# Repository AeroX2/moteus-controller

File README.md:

# moteus-controller

A custom servo BLDC driver loosely based on the [mjbots Moteus r4.11](https://github.com/mjbots/moteus/tree/main/hw/controller/r4.11) hardware.

Main differences from upstream Moteus r4.11:

- **STSPIN32G4** integrated gate driver + STM32G431 instead of separate DRV8353S and MCU.
- Schematic and BOM trimmed/substituted for **JLCPCB** assembly.
- **AS5048A** magnetic encoder.
- **MAX3051** CAN transceiver.
- Firmware built on **SimpleFOC** + Arduino-stm32duino instead of the mjbots firmware.

## Repository layout

```
moteus-controller/
├── pcb/                # KiCad schematic + PCB
├── firmware/           # SimpleFOC-based motor controller firmware (PlatformIO + Arduino)
├── bootloader/         # OpenBLT bootloader for STM32G431VB  (submodule -> AeroX2/OpenBLT-STM32)
└── openblt/            # OpenBLT library + mjbots fdcanusb driver (submodule -> AeroX2/openblt)
```

`firmware/`, `bootloader/`, and `openblt/` each have their own build setup and README.

## Quick build / flash

Prerequisites: [PlatformIO Core](https://platformio.org/install/cli), an ST-Link, optionally a [mjbots fdcanusb](https://github.com/mjbots/fdcanusb) for CAN-FD uploads.

Clone with submodules:

```bash
git clone --recurse-submodules https://github.com/AeroX2/moteus-controller.git
cd moteus-controller
```

Flash the bootloader once (writes at `0x08000000`, ~8 KB):

```bash
pio run -d bootloader -e moteus_g431 -t upload
```

Flash the application (writes at `0x08005000`):

```bash
pio run -d firmware -e moteus -t upload
```

Power-cycle the board; the bootloader runs for ~3 s, then jumps to the app.

After the bootloader is in place, subsequent firmware uploads can go over CAN-FD via fdcanusb (no ST-Link needed):

```bash
pio run -d firmware -e moteus_openblt_can -t upload
```

## Bootloader

`bootloader/` is a bare-metal **stm32cube + PlatformIO** port of the upstream [Feaser OpenBLT](https://github.com/feaser/openblt) Nucleo-G431 demo, adapted for the moteus-controller hardware:

- HSI → PLL → 170 MHz (no HSE crystal on this board).
- FDCAN1 routed to PA11/PA12 (vs Nucleo's PB8/PB9).
- 20 KB reserved at `0x08000000`; app starts at `0x08005000`; the final 2 KB flash page (`0x0801F800`) is reserved for application PID storage and never touched by the bootloader.

OpenBLT library + STM32G4 port sources are compiled directly from the `openblt/` submodule by `bootloader/src/build.py` — there are no local copies of those files in `bootloader/`, so updating to a newer OpenBLT is just a submodule bump.

## CAN-FD upload (`moteus_openblt_can` env)

The CAN-FD upload path uses a custom **mjbots fdcanusb** host driver added to LibOpenBLT (see `openblt/Host/Source/LibOpenBLT/port/windows/canif/fdcanusb/`) plus a small wrapper (`firmware/host_openblt_flash/`) and a Python harness (`firmware/scripts/openblt_host_upload.py`) that handles pre-reset, device discovery, and srec conversion.

Build the host tool once:

```bash
python firmware/scripts/build_host_openblt_flash.py
```

Then `pio run -d firmware -e moteus_openblt_can -t upload` does the rest.

Tuning knobs live in `firmware/platformio.ini` under `[env:moteus_openblt_can]`:

- `custom_openblt_can_device` — fdcanusb COM port and USB baud.
- `custom_openblt_can_tid` / `custom_openblt_can_rid` — XCP CAN IDs (default `667` / `7E1`, must match `bootloader/src/blt_conf.h`).
- `custom_openblt_reset_discover` / `custom_openblt_reset_target_id` — control how the running application is asked to reboot into the bootloader before uploading.

## License

The original mjbots Moteus design is licensed under Apache 2.0; see `LICENSE`. OpenBLT and its derivatives are GPLv3 (see `openblt/Doc/license.html`).

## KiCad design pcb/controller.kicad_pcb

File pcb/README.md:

# moteus-controller

## Schematic

## PCB
https://kicanvas.org/?github=https%3A%2F%2Fgithub.com%2FAeroX2%2Fmoteus-controller%2Ftree%2Fmain%2Fpcb

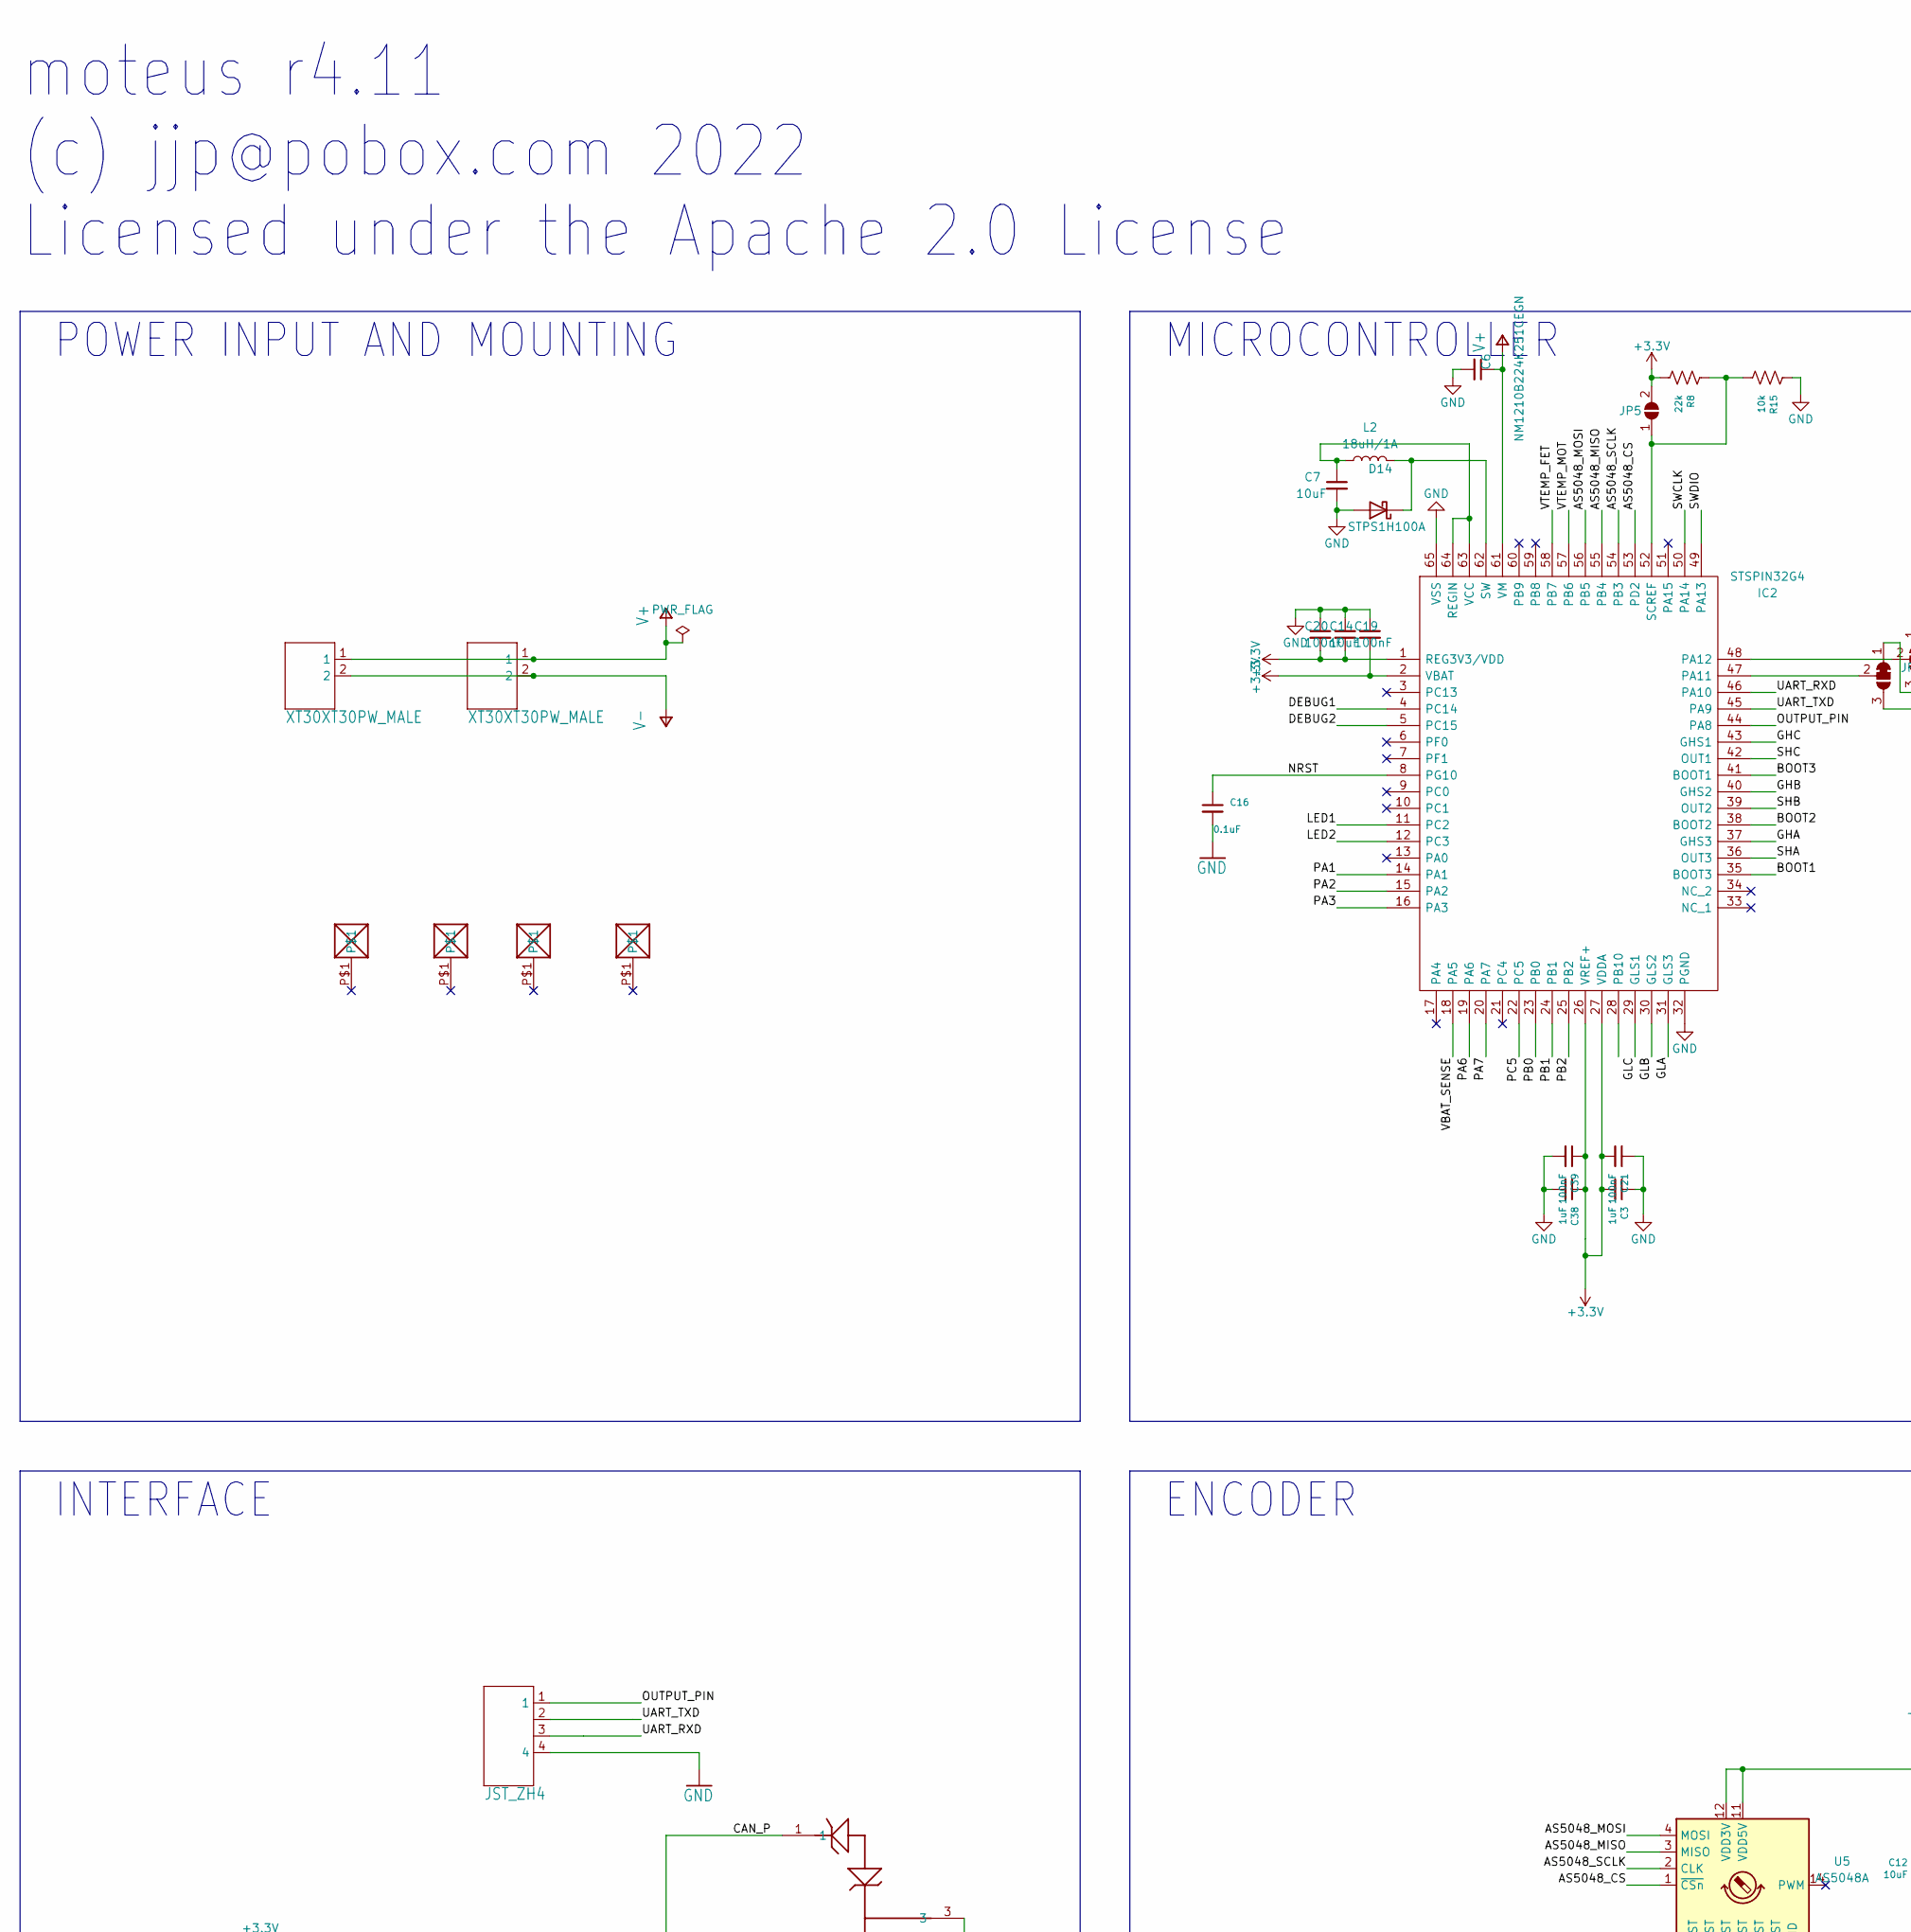
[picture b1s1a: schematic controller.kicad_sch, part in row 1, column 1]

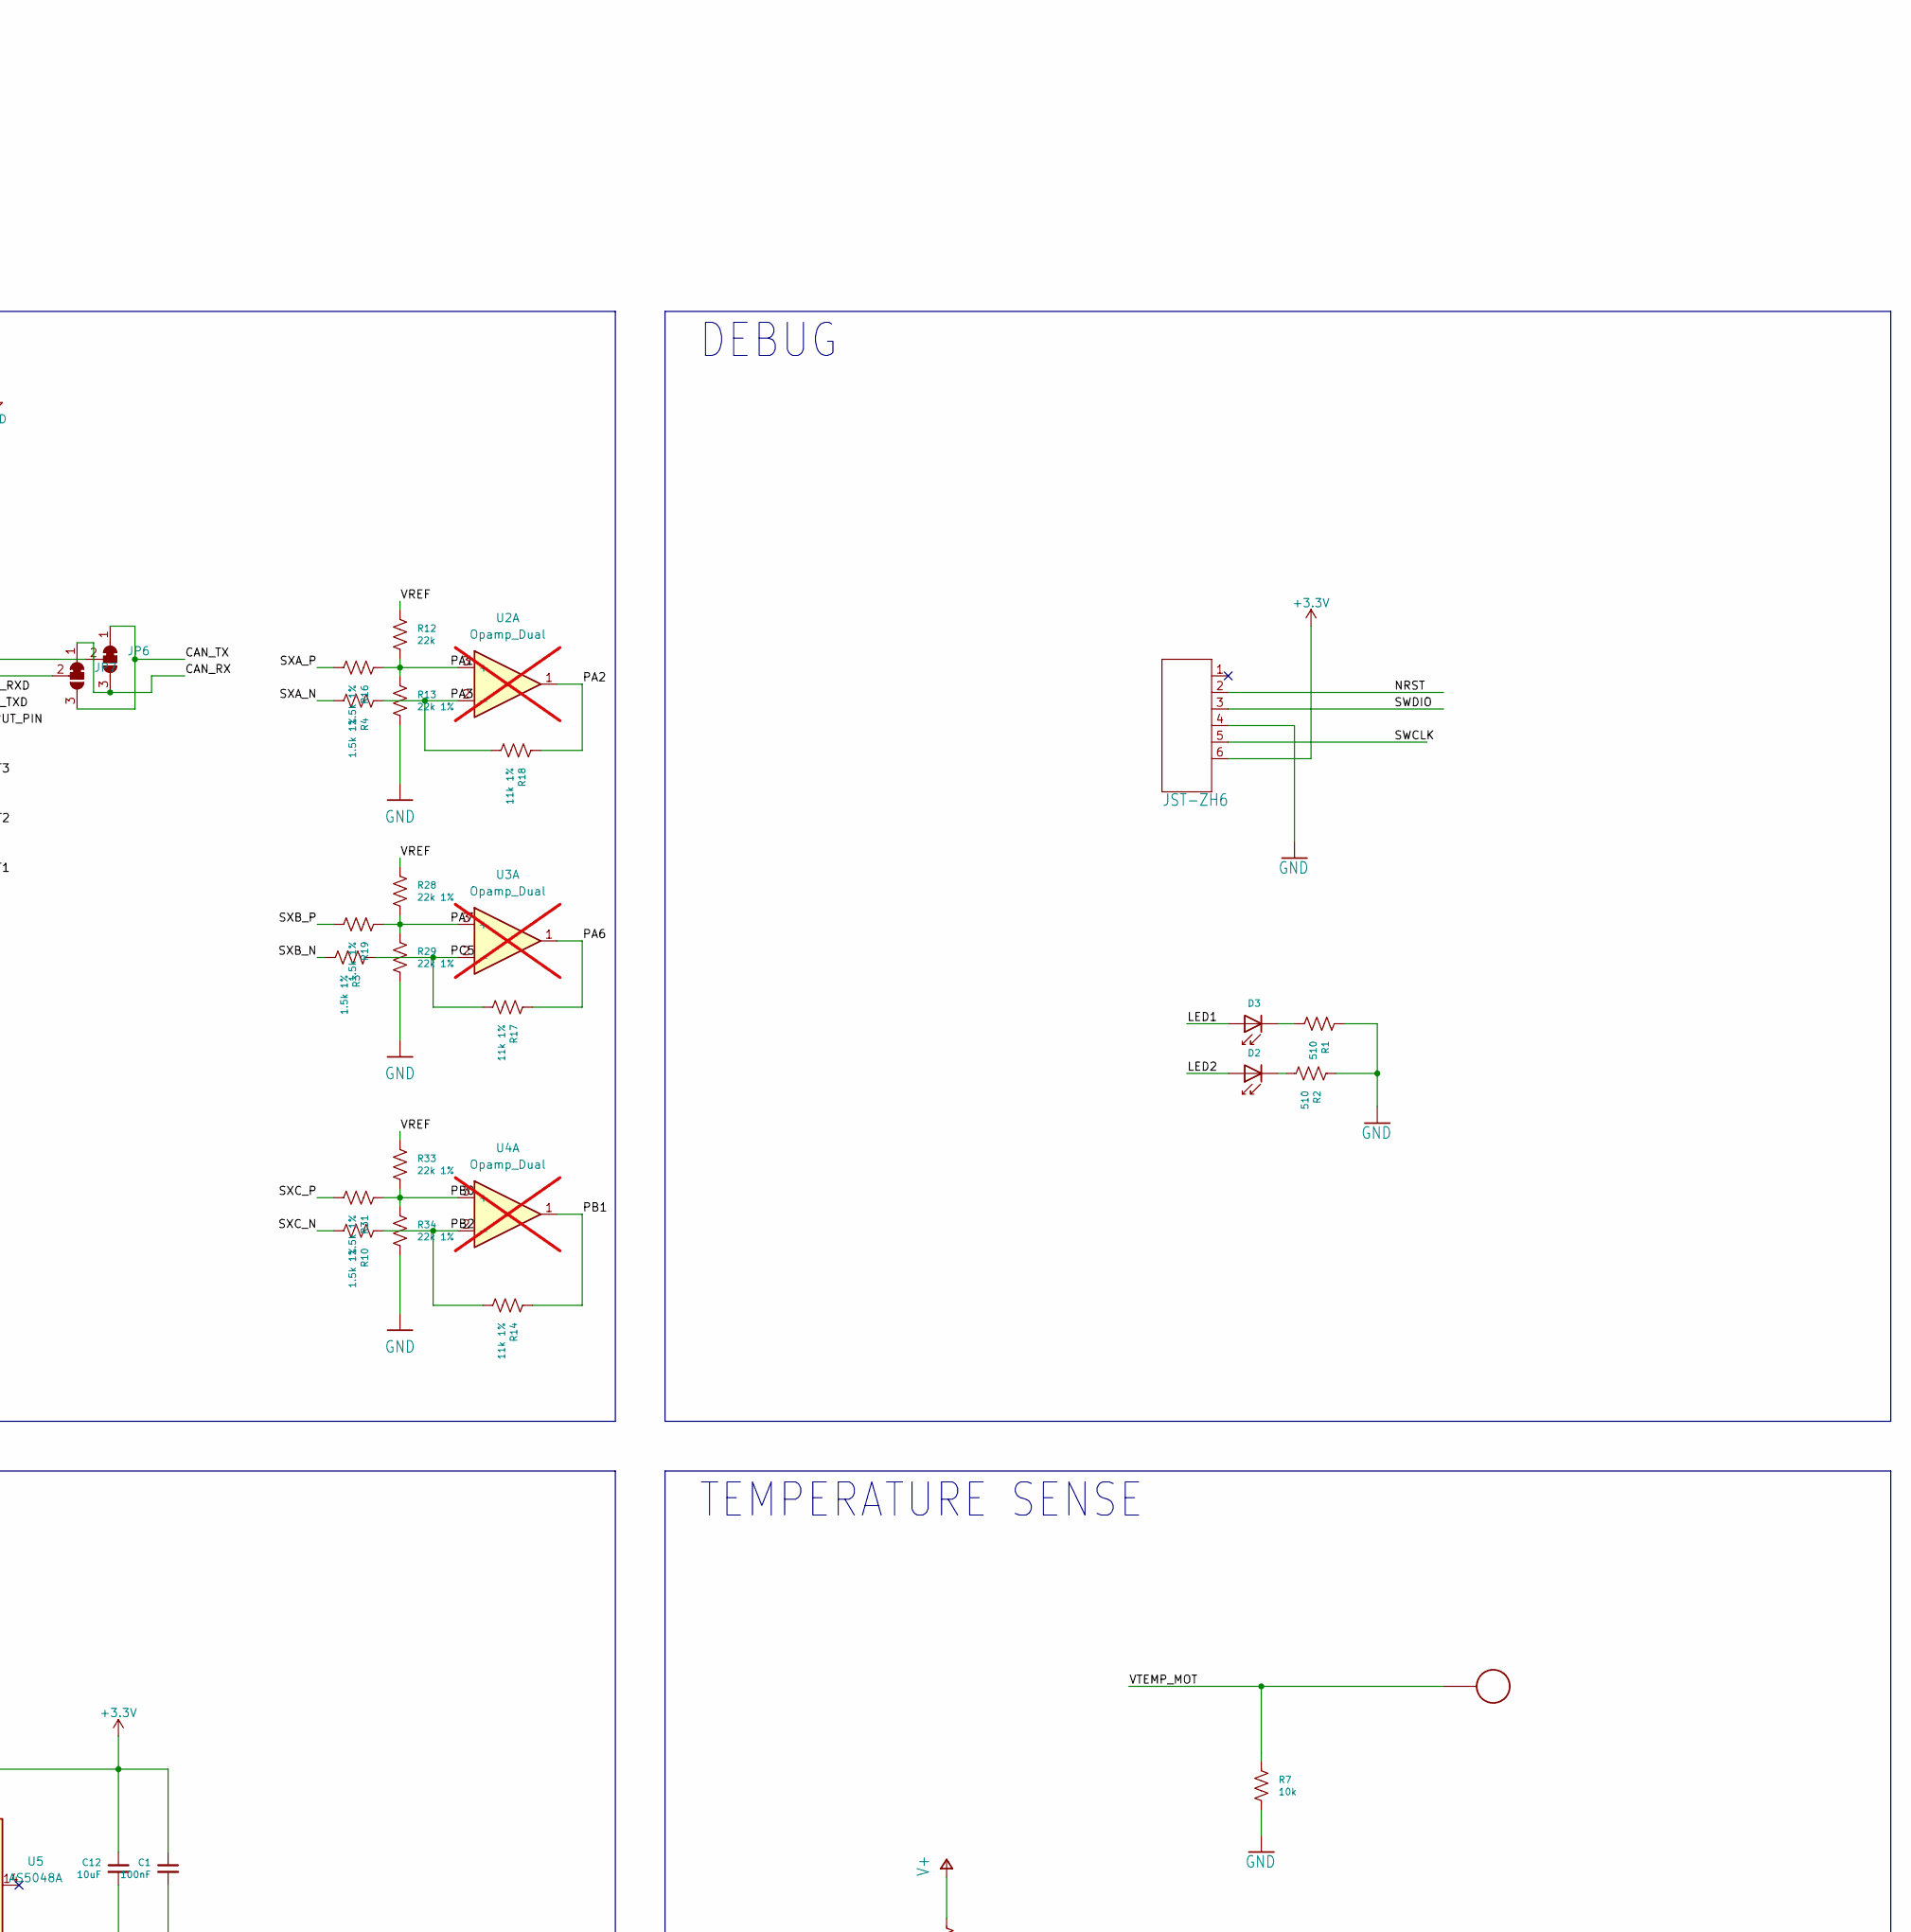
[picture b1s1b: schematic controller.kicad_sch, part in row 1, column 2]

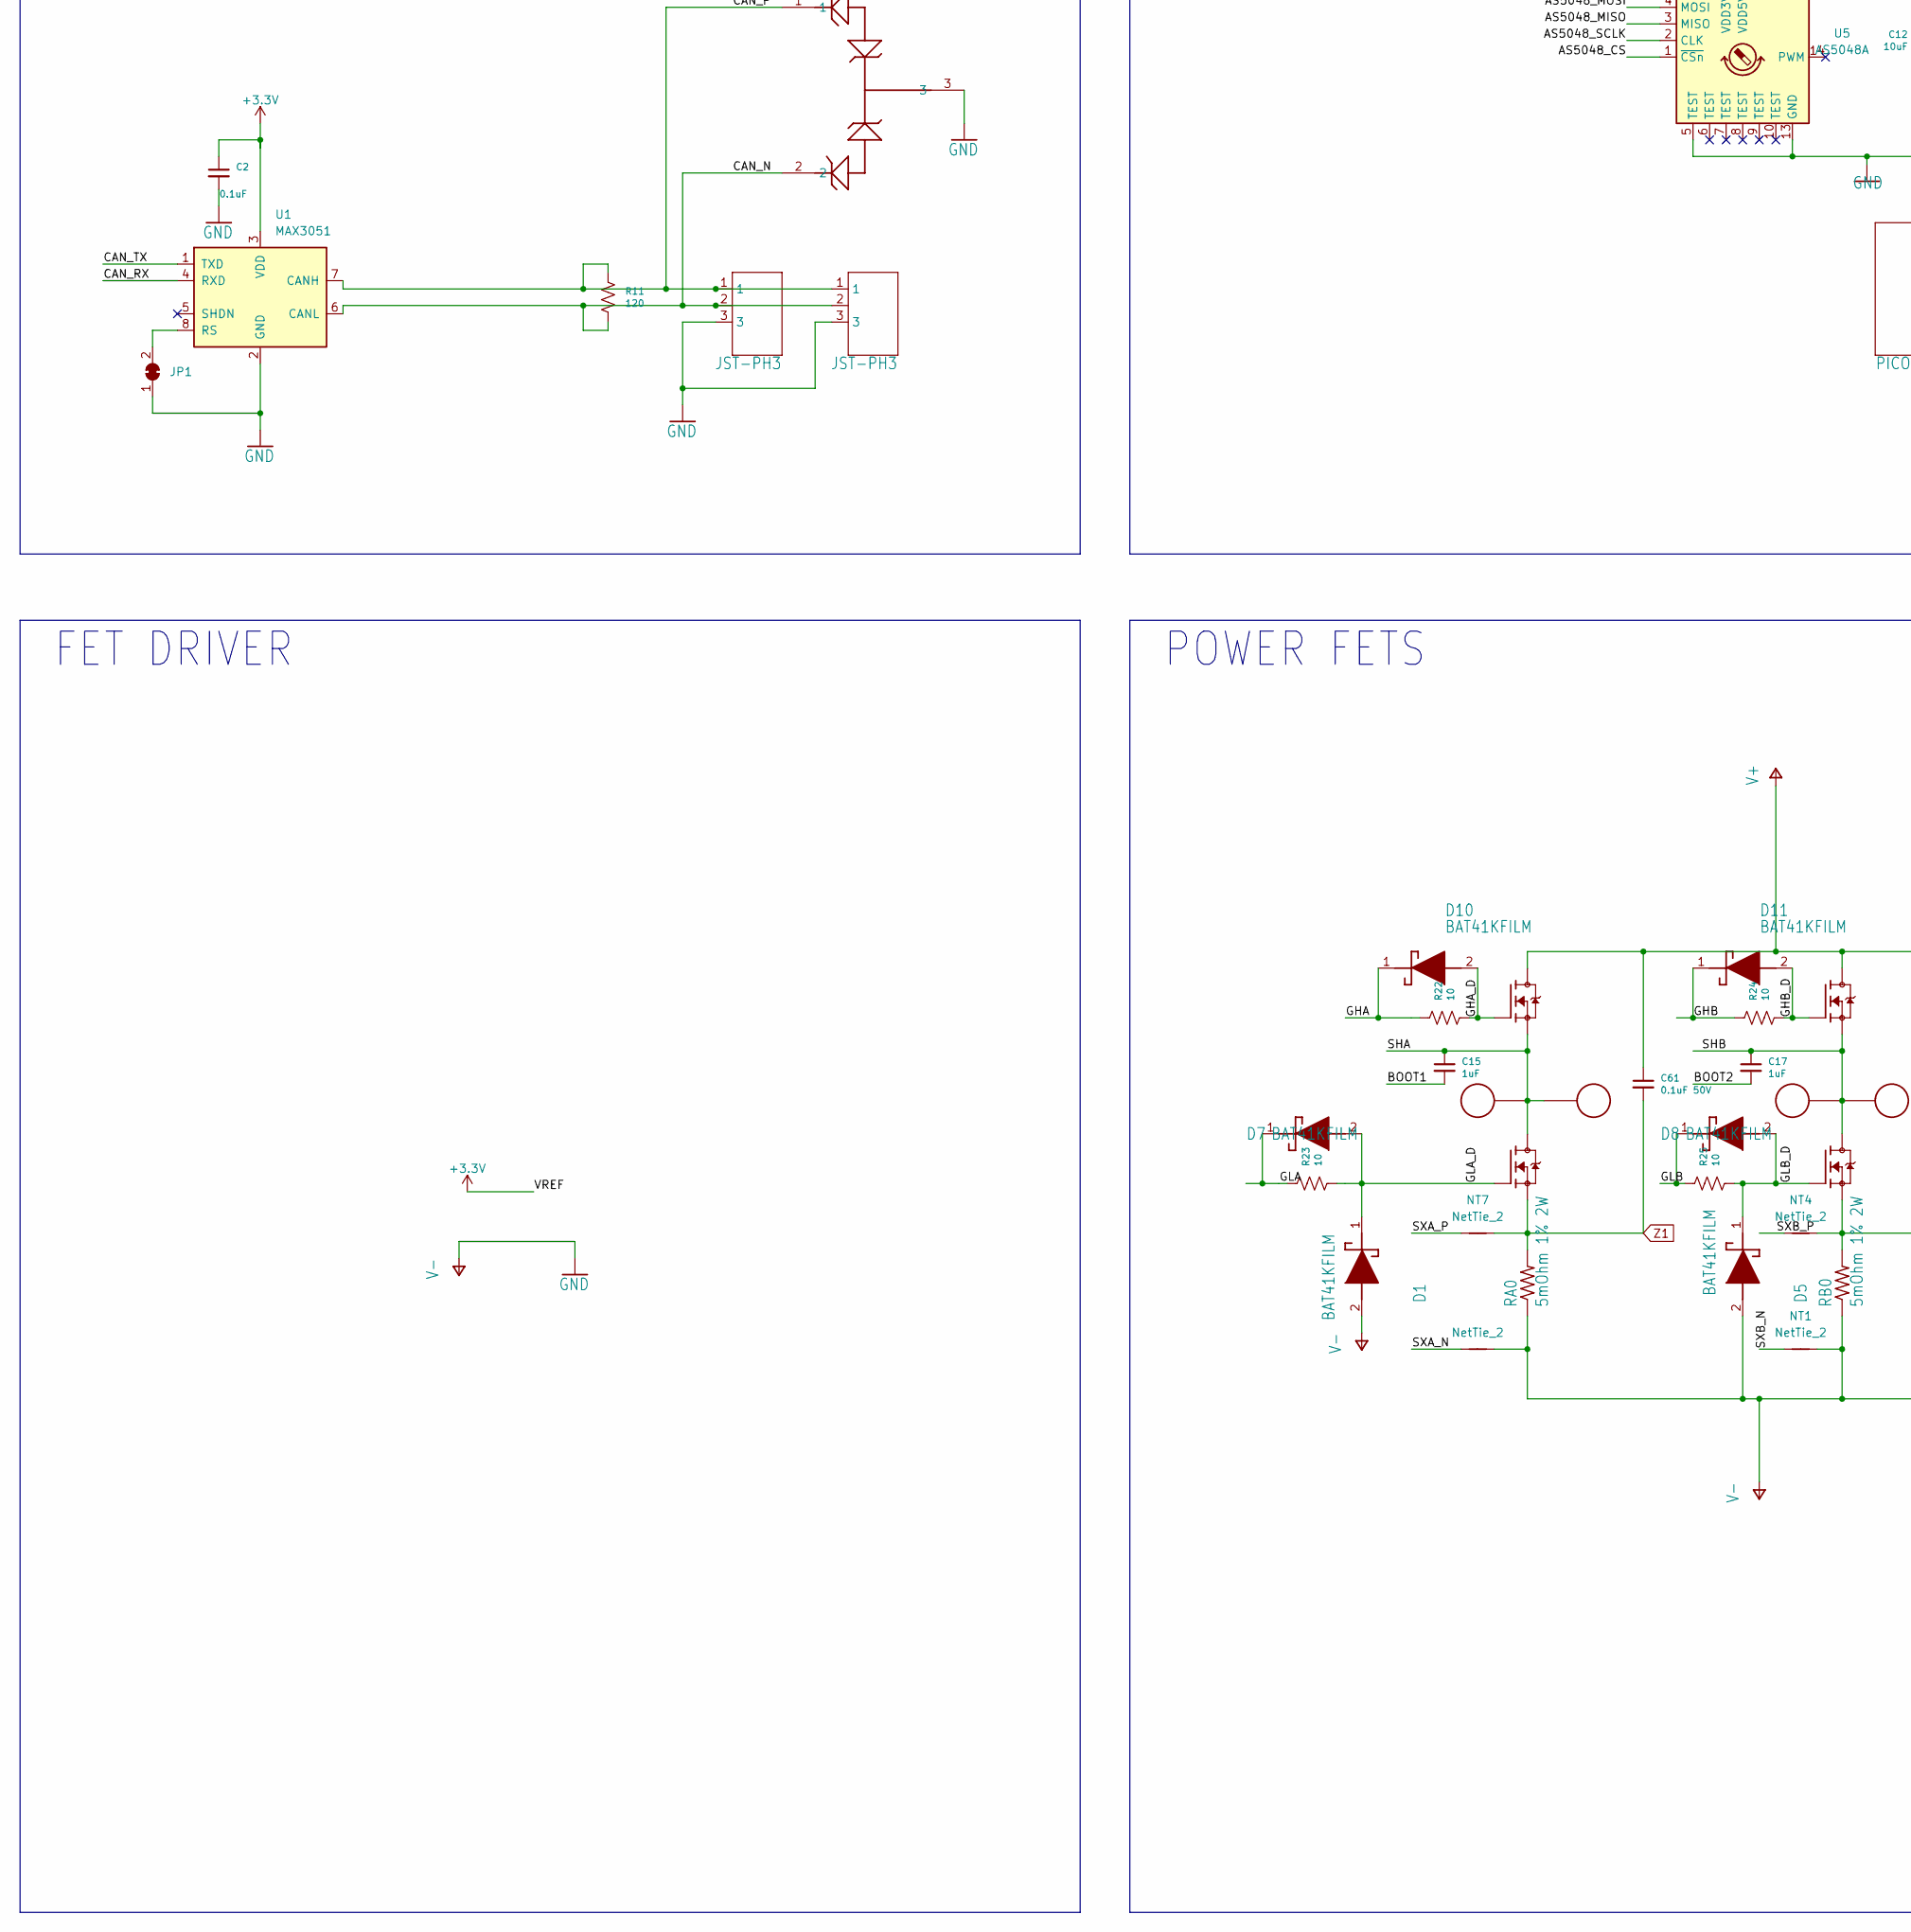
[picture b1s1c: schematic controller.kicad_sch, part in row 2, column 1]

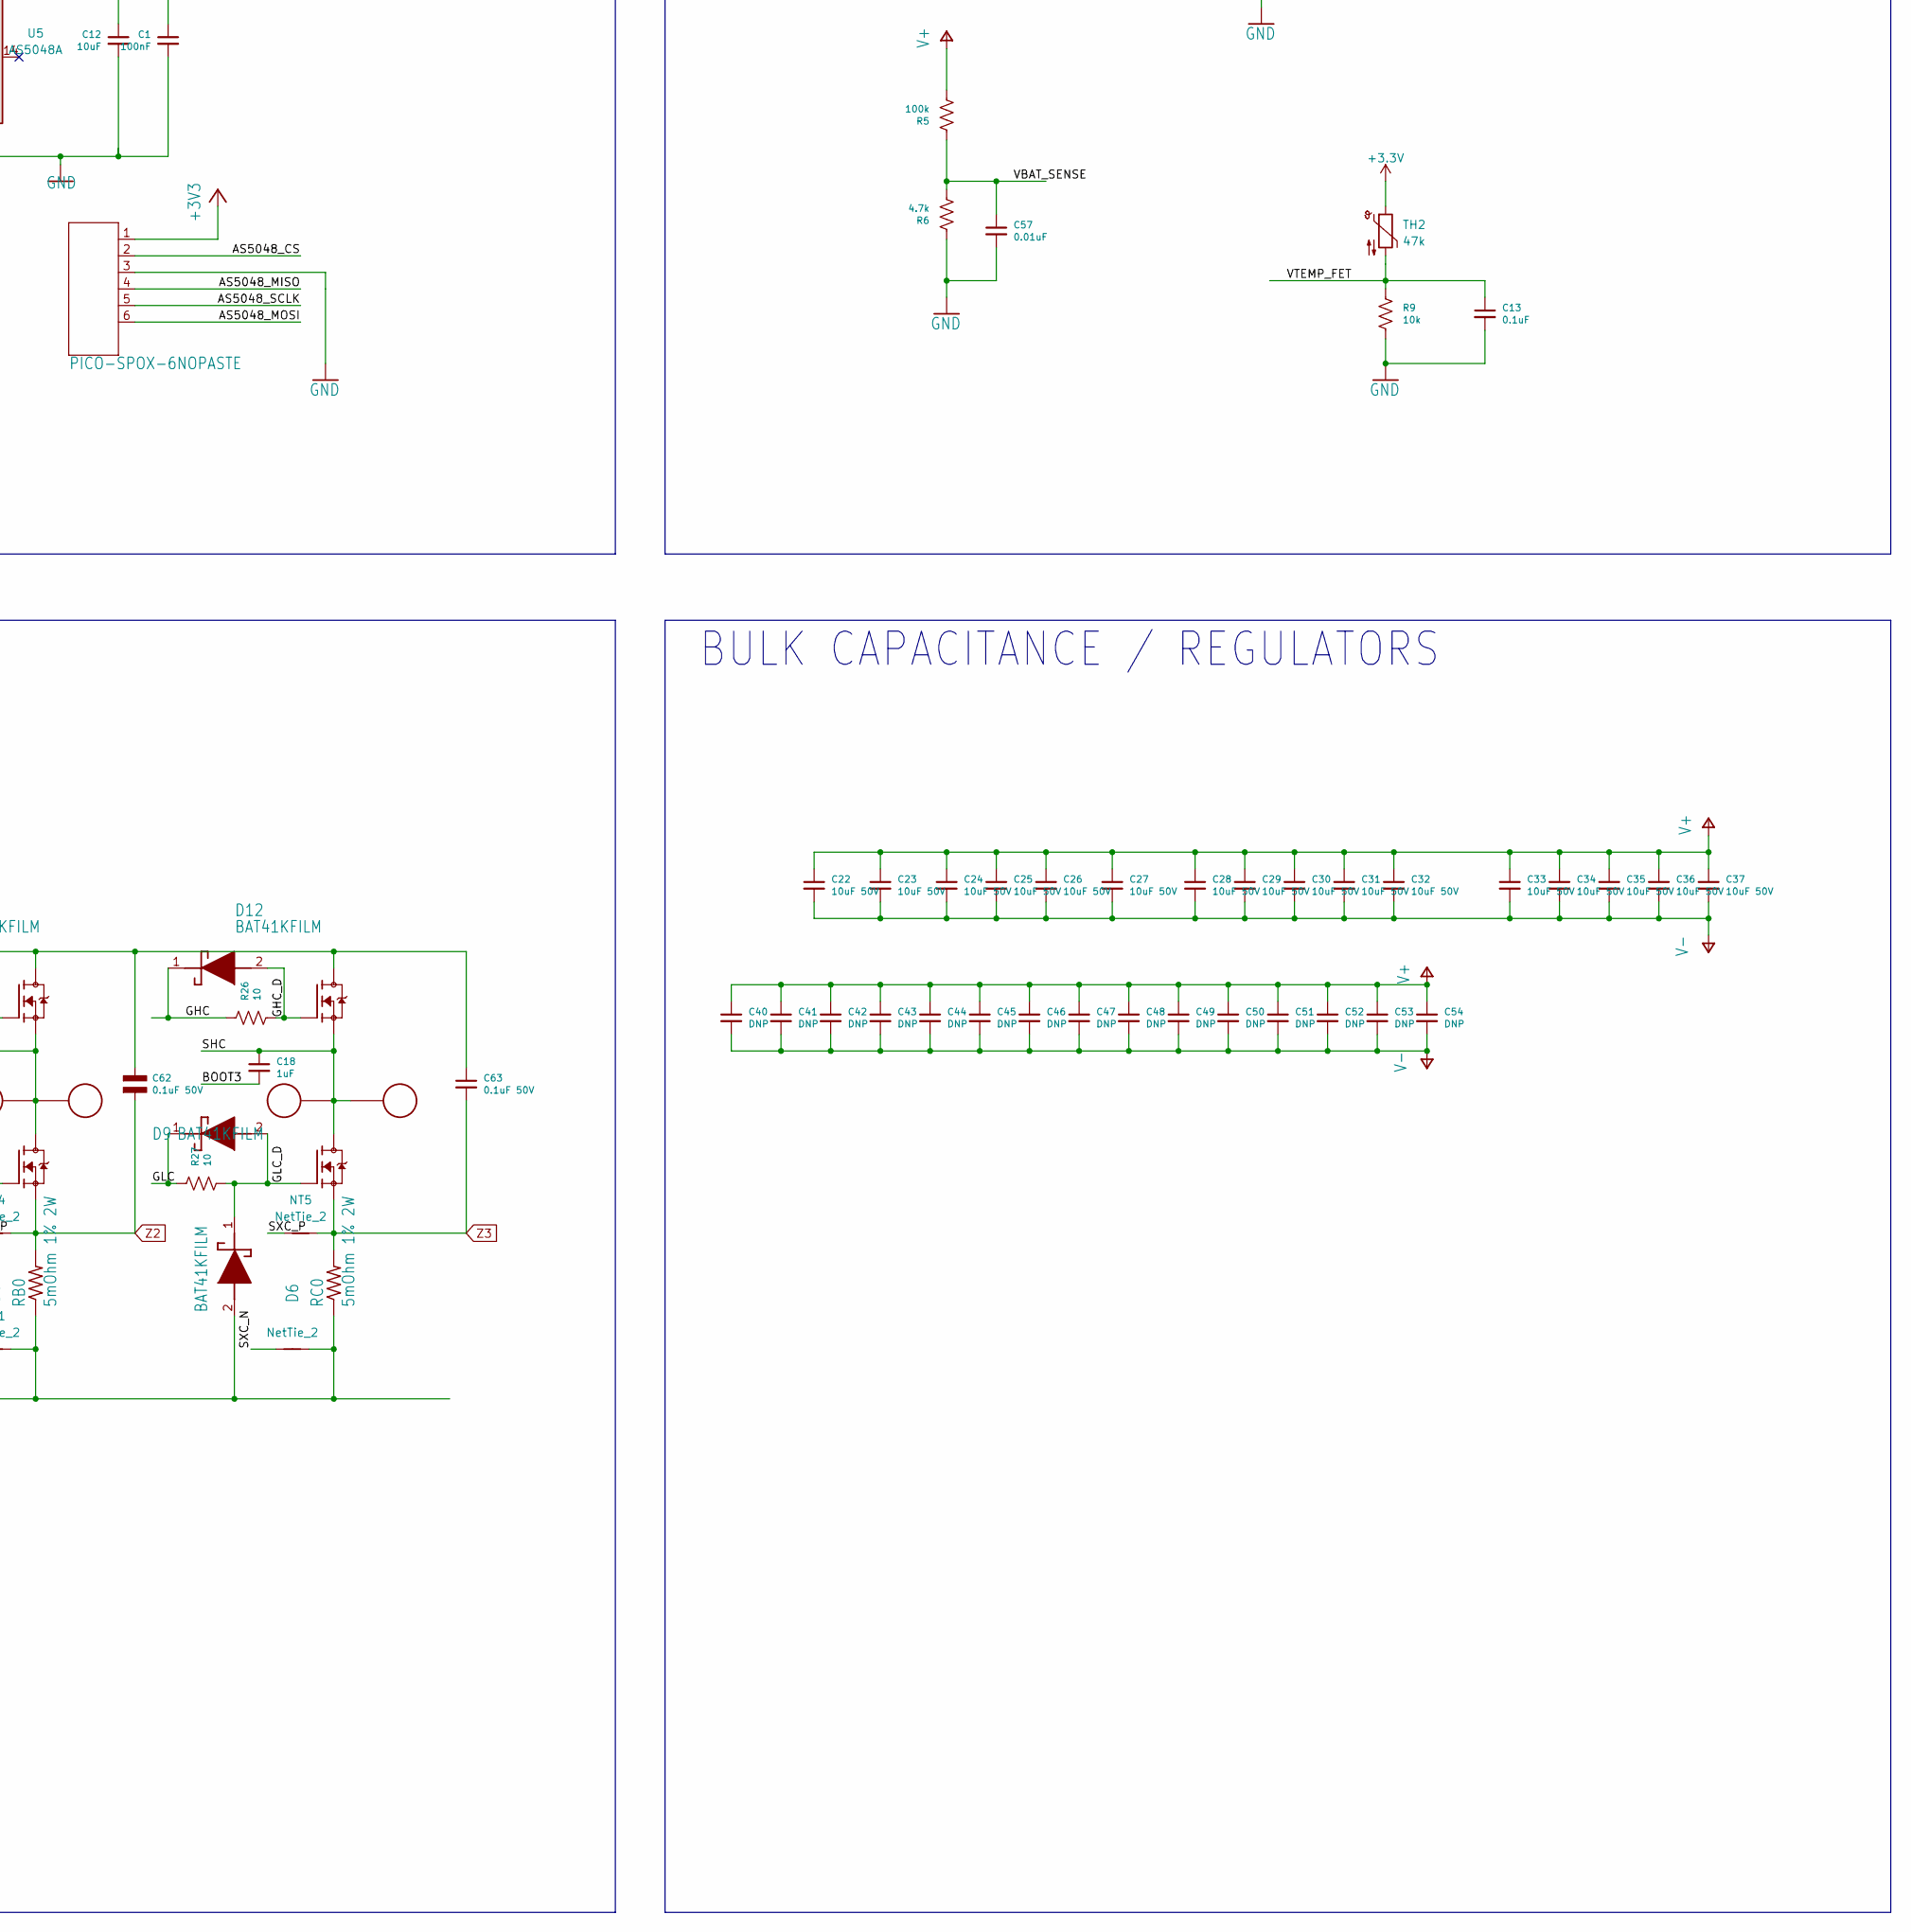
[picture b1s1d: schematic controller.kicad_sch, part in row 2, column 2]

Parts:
A0: PAD16AWG_PAD; 16AWG_PAD
ABS0: JST_ZH4; JST_S4B-ZR-SM4A-TF(LF)(SN); MPN S4B-ZR-SM4A-TF(LF)(SN)
B0: PAD16AWG_PAD; 16AWG_PAD
C0: PAD16AWG_PAD; 16AWG_PAD
C1: 100nF; C_0402_1005Metric; MPN MF-CAP-0402-0.1uF
C2, C13, C16: 0.1uF; C_0402_1005Metric; MPN MF-CAP-0402-0.1uF
C3, C15, C17, C18, C38: 1uF; C_0402_1005Metric; MPN MF-CAP-0402-1uF
C6: NM1210B224K251CEGN; C_1210_3225Metric
C7, C14: 10uF; C_0402_1005Metric
C12: 10uF; C_0402_1005Metric; MPN MF-CAP-0402-0.1uF
C19, C20: 100nF; C_0402_1005Metric
C21, C39: 100nF; C_0402_1005Metric; MPN MF-CAP-0402-1uF
C22, C23, C24, C25, C26, C27, C28, C29, C30, C31, C32, C33, C34, C35, C36, C37: 10uF 50V; C_1206_3216Metric; MPN C3216X7R1H106K160AE
C40, C41, C42, C43, C44, C45, C46, C47, C48, C49, C50, C51, C52, C53, C54: DNP; C_1206_3216Metric
C57: 0.01uF; C_0402_1005Metric; MPN MF-CAP-0402-0.01uF
C61, C63: 0.1uF 50V; C_1206_3216Metric; MPN 12065C104KAZ2A
C62: 0.1uF 50V; C0603_NOBORDER; MPN 06035C104KAZ2A
CAN1, CAN2: JST-PH3; JST_S3B-PH-SM4-TB(LF)(SN); MPN S3B-PH-SM4-TB(LF)(SN)
D1, D5, D6, D7, D8, D9, D10, D11, D12: BAT41KFILM; SODFL1608X70N; MPN BAT41KFILM
D2: MF-LED-0603-RED; LED_0603_1608Metric; MPN MF-LED-0603-GREEN
D3: MF-LED-0603-RED; LED_0603_1608Metric
D4: DUAL_TVS; SOT23-3; MPN CDSOT23-0502B
D14: STPS1H100A; D_SMA
DA0: PAD24AWG_PAD; 24AWG_PAD
DB0: PAD24AWG_PAD; 24AWG_PAD
DC0: PAD24AWG_PAD; 24AWG_PAD
ENC0: PICO-SPOX-6NOPASTE; PICO-SPOX-SMT-RA-6-NOPASTE
IC2: STSPIN32G4; QFN50P900X900X100-65N-D; Manufacturer_Part_Number STSPIN32G4; Mouser Part Number 511-STSPIN32G4
J1, J2: XT30XT30PW_MALE; XT30PW_MALE
JP1: SolderJumper_2_Bridged; SolderJumper-2_P1.3mm_Bridged_Pad1.0x1.5mm
JP5: SolderJumper_2_Open; SolderJumper-2_P1.3mm_Open_RoundedPad1.0x1.5mm
JP6, JP7: SolderJumper_3_Bridged12; SolderJumper-3_P1.3mm_Bridged12_RoundedPad1.0x1.5mm
L2: 18uH/1A; IND-SMD_L5.8-W5.2_SCD0503T
M1, M2, M3, M4: MOUNT; MountingHole_3.2mm_M3_DIN965_Pad
NT1, NT4, NT5, NT6, NT7, NT8: NetTie_2; NetTie-2_SMD_Pad0.2mm
Q1, Q3, Q5: TPH1R204PLSOP_ADVANCE_8; SOP_ADVANCE_8; MPN TPH2R506PL,L1Q
Q2, Q4, Q6: TPH1R204PLSOP_ADVANCE_8; SOP_ADVANCE_8; MPN TPH4R50ANH,L1Q(M
R1, R2: 510; R_0402_1005Metric; MPN MF-RES-0402-560
R3, R4, R10, R16, R19, R31: 1.5k 1%; R_0402_1005Metric; MPN MF-RES-0402-2K
R5: 100k; R_0402_1005Metric; MPN RC0402FR-07100KL
R6: 4.7k; R_0402_1005Metric; MPN RC0402FR-074K7L
R7, R9: 10k; R_0402_1005Metric; MPN RC0402FR-0710KL
R8, R12: 22k; R_0402_1005Metric; MPN MF-RES-0402-2K
R11: 120; R_0402_1005Metric; MPN MF-RES-0402-2K
R13, R28, R29, R33, R34: 22k 1%; R_0402_1005Metric; MPN MF-RES-0402-2K
R14, R17, R18: 11k 1%; R_0402_1005Metric; MPN MF-RES-0402-2K
R15: 10k; R_0402_1005Metric; MPN MF-RES-0402-2K
R22, R23, R24, R25, R26, R27: 10; R_0402_1005Metric; MPN RC0402FR-077R5L
RA0: 5mOhm 1% 2W; R_1206_3216Metric; MPN HCS1206FTL500
RB0: 5mOhm 1% 2W; R_1206_3216Metric; MPN HCS1206FTL500
RC0: 5mOhm 1% 2W; R_1206_3216Metric; MPN HCS1206FTL500
SWD0: JST-ZH6; JST_S6B-ZR-SM4A-TF(LF)(SN); MPN S6B-ZR-SM4A-TF(LF)(SN)
TEMP2: PAD24AWG_PAD; 24AWG_PAD
TH2: 47k; R_0603_1608Metric
U1: MAX3051; TSOT-23-8
U2, U3, U4: Opamp_Dual; not fitted
U5: AS5048A; TSSOP-14_4.4x5mm_P0.65mm

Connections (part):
+3.3V: C1.1, C2.1, C3.2, C12.1, C14.2, C19.2, C20.2, C21.2, C38.1, C39.1, IC2.1 (REG3V3/VDD), IC2.2 (VBAT), IC2.26 (VREF+), IC2.27 (VDDA), JP5.2 (B), R8.2, R12.1, R28.1, R33.1, SWD0.6, TH2.1, U1.3 (VDD), U5.11 (VDD5V), U5.12 (VDD3V)
+3V3: ENC0.1
/AS5048_CS: ENC0.2, IC2.53 (PD2), U5.1 (~CSn)
/AS5048_MISO: ENC0.4, IC2.55 (PB4), U5.3 (MISO)
/AS5048_MOSI: ENC0.6, IC2.56 (PB5), U5.4 (MOSI)
/AS5048_SCLK: ENC0.5, IC2.54 (PB3), U5.2 (CLK)
/BOOT1: C15.2, IC2.35 (BOOT3)
/BOOT2: C17.2, IC2.38 (BOOT2)
/BOOT3: C18.2, IC2.41 (BOOT1)
/CAN_N: CAN1.2, CAN2.2, D4.2, R11.2, U1.6 (CANL)
/CAN_P: CAN1.1, CAN2.1, D4.1, R11.1, U1.7 (CANH)
/CAN_RX: JP6.3 (B), JP7.1 (A), U1.4 (RXD)
/CAN_TX: JP6.1 (A), JP7.3 (B), U1.1 (TXD)
/DEBUG1: IC2.4 (PC14)
/DEBUG2: IC2.5 (PC15)
/GHA: D10.1 (K), IC2.37 (GHS3), R22.1
/GHA_D: D10.2 (A), Q1.4 (G), R22.2
/GHB: D11.1 (K), IC2.40 (GHS2), R24.1
/GHB_D: D11.2 (A), Q3.4 (G), R24.2
/GHC: D12.1 (K), IC2.43 (GHS1), R26.1
/GHC_D: D12.2 (A), Q5.4 (G), R26.2
/GLA: D7.1 (K), IC2.31 (GLS3), R23.1
/GLA_D: D1.1 (K), D7.2 (A), Q2.4 (G), R23.2
/GLB: D8.1 (K), IC2.30 (GLS2), R25.1
/GLB_D: D5.1 (K), D8.2 (A), Q4.4 (G), R25.2
/GLC: D9.1 (K), IC2.29 (GLS1), R27.1
/GLC_D: D6.1 (K), D9.2 (A), Q6.4 (G), R27.2
/LED1: D3.2 (A), IC2.11 (PC2)
/LED2: D2.2 (A), IC2.12 (PC3)
/NRST: C16.1, IC2.8 (PG10), SWD0.2
/OUTPUT_PIN: ABS0.1, IC2.44 (PA8)
/PA1: IC2.14 (PA1), R12.2, R13.1, R16.1, U2.3 (+)
/PA2: IC2.15 (PA2), R18.1, U2.1
/PA3: IC2.16 (PA3), R4.1, R18.2, U2.2 (-)
/PA6: IC2.19 (PA6), R17.1, U3.1
/PA7: IC2.20 (PA7), R19.1, R28.2, R29.1, U3.3 (+)
/PB0: IC2.23 (PB0), R31.1, R33.2, R34.1, U4.3 (+)
/PB1: IC2.24 (PB1), R14.1, U4.1
/PB2: IC2.25 (PB2), R10.1, R14.2, U4.2 (-)
/PC5: IC2.22 (PC5), R3.1, R17.2, U3.2 (-)
/SHA: A0.1, C15.1, DA0.P$1, IC2.36 (OUT3), Q1.1 (S), Q1.2 (S), Q1.3 (S), Q2.5 (D), Q2.6 (D), Q2.7 (D), Q2.8 (D), Q2.PAD (D)
/SHB: B0.1, C17.1, DB0.P$1, IC2.39 (OUT2), Q3.1 (S), Q3.2 (S), Q3.3 (S), Q4.5 (D), Q4.6 (D), Q4.7 (D), Q4.8 (D), Q4.PAD (D)
/SHC: C0.1, C18.1, DC0.P$1, IC2.42 (OUT1), Q5.1 (S), Q5.2 (S), Q5.3 (S), Q6.5 (D), Q6.6 (D), Q6.7 (D), Q6.8 (D), Q6.PAD (D)
/SWCLK: IC2.50 (PA14), SWD0.5
/SWDIO: IC2.49 (PA13), SWD0.3
/SXA_N: NT8.1, R4.2
/SXA_P: NT7.1, R16.2
/SXB_N: NT1.1, R3.2
/SXB_P: NT4.1, R19.2
/SXC_N: NT6.1, R10.2
/SXC_P: NT5.1, R31.2
/UART_RXD: ABS0.3, IC2.46 (PA10)
/UART_TXD: ABS0.2, IC2.45 (PA9)
/VBAT_SENSE: C57.1, IC2.18 (PA5), R5.1, R6.2
/VTEMP_FET: C13.1, IC2.58 (PB7), R9.1, TH2.2
/VTEMP_MOT: IC2.57 (PB6), R7.1, TEMP2.P$1
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
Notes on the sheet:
DEBUG
POWER FETS
moteus r4.11 (c) jjp@pobox.com 2022 Licensed under the Apache 2.0 License
ENCODER
BULK CAPACITANCE / REGULATORS
INTERFACE
MICROCONTROLLER
FET DRIVER
TEMPERATURE SENSE
POWER INPUT AND MOUNTING

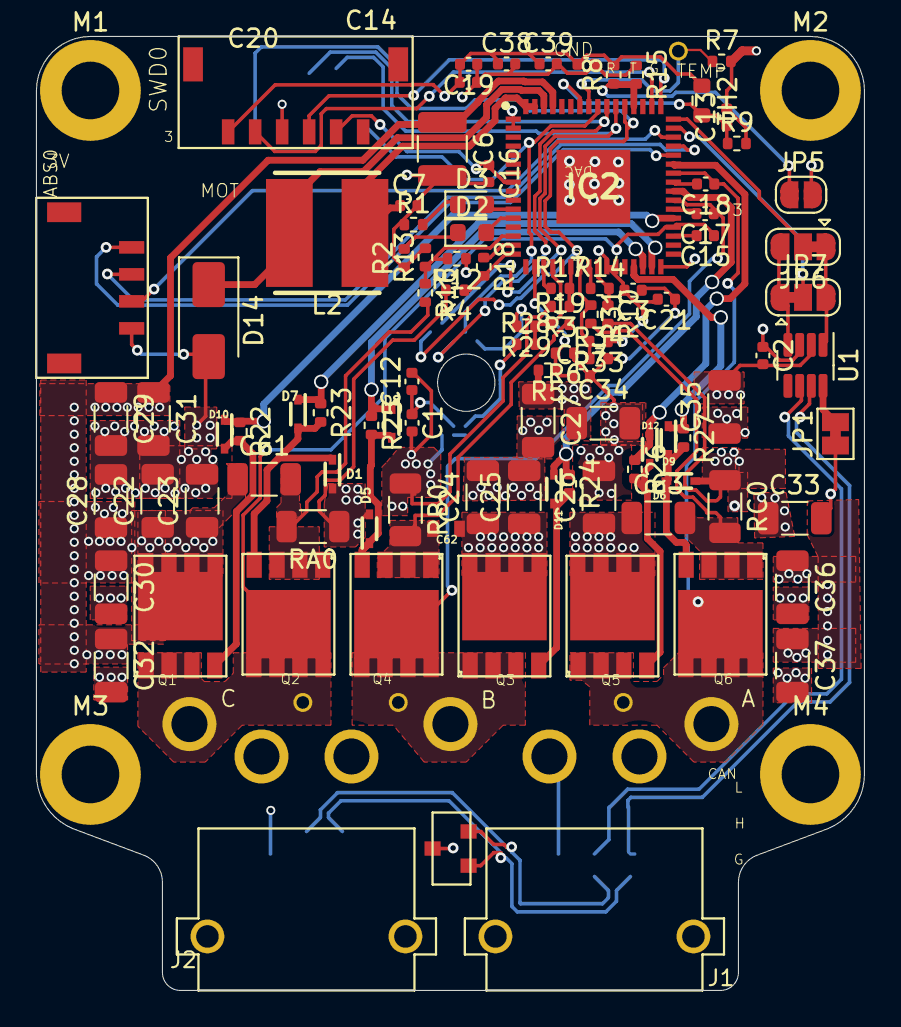
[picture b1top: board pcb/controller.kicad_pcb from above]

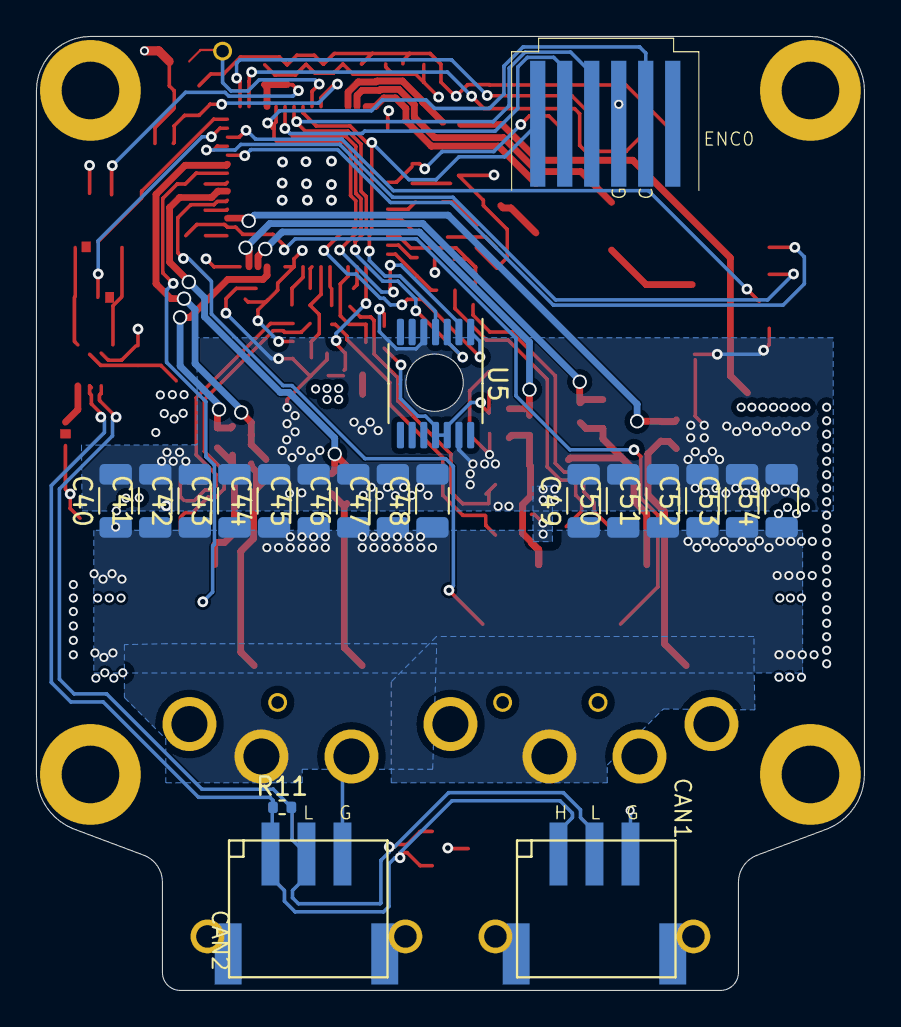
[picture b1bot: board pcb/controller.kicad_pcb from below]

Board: 4 copper layers, 46.0 x 53.0 mm, 137 parts (20 on the bottom side), 66 nets.

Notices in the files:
controller.kicad_pcb:
(c) 2022
